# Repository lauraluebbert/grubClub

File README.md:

# grubClub
Please cite the information in this repository using the following DOI:  

I would like to present grubClub (“grub” for larva, and “club” for… well, you will see). I built off of the ethoscope (https://github.com/gilestrolab/ethoscope) by https://github.com/qgeissmann to enable automated long-term optogenetic stimulation of Drosophila larvae. Here is my Halloween-style release: https://twitter.com/NeuroLuebbert/status/1454220954666631170?s=20

GrubClub consists of a printed circuit board (PCB) and an accompanying arena. Both fit into the ethoscope published here: https://journals.plos.org/plosbiology/article?id=10.1371/journal.pbio.2003026.

The PCB holds 4 transistors, each connecting to 2 LEDs. Each row of LEDs can be controlled independently through Raspberry Pi GPIOs. In the picture below, each LED has a 270 ohm resistor. The power of the LEDs can be increased (or decreased) by modifying this resistance (within the circuit limits). 

The grubClub arena slides into the ethoscope and holds larvae in small round wells that can be filled with sugar-containing agar (or any larva medium). Each square fits a standard 22x22 mm coverslip as a lid. I 3D-printed my arena using translucent PLA to increase light intensity.

Since I am currently not recording larval behavior, I did not include an IR backlight for camera recordings. However, the PCB is designed such that an IR light strip can easily fit between the LED rows, enabling optogenetic stimulation and behavior recording at the same time. Finally, while red LEDs (~630 nm) might prevent a startle response, for my experimental design, I decided to stimulate at the spectral peak of my channelrhodopsin Chrimson (590 nm). The PCB supports LEDs of any color, and I included both options in the component list.

[grubClub PCB](https://user-images.githubusercontent.com/56094636/139601286-2ef72724-cccf-4f6b-9c9d-bd818d46505a.mp4)

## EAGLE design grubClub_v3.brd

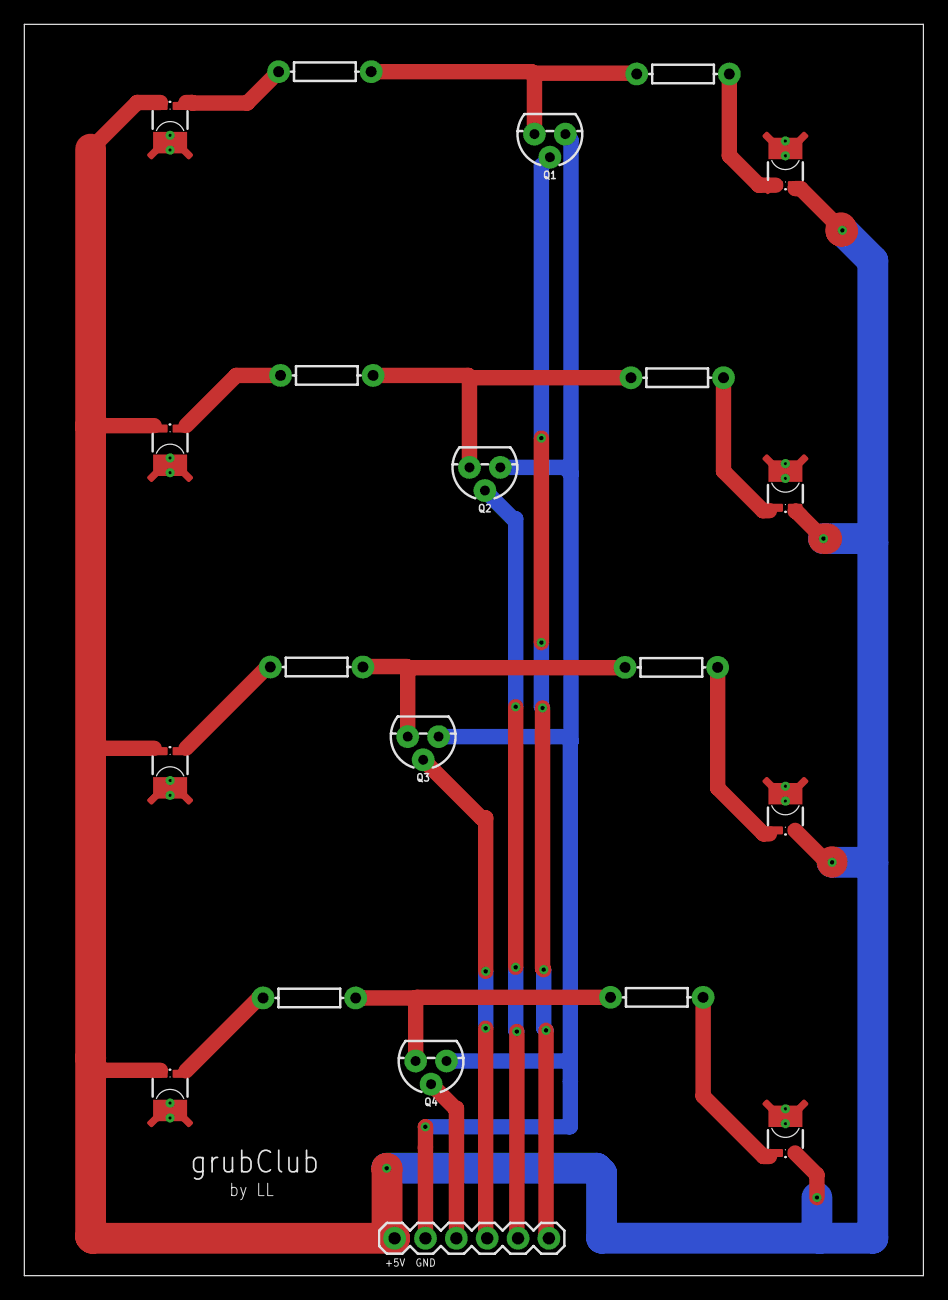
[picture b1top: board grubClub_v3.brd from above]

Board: 2 copper layers, 74.0 x 103.0 mm, 21 parts (0 on the bottom side), 20 nets.

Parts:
J6: 1X06
LED1, LED2, LED3, LED4, LED5, LED6, LED7, LED8: LUXEON_REBEL
Q1, Q2, Q3, Q4: 200mA/40V; TO-92
R1, R2, R3, R4, R5, R6, R7, R8: AXIAL-0.3

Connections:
unnamed: LED7.C, LED7.C@1, R1.P$1
unnamed: J6.4, Q4.2
unnamed: J6.3, Q3.2
unnamed: J6.2, Q2.2
unnamed: J6.1, Q1.2
unnamed: LED1.C, LED1.C@1, R4.P$1
unnamed: J6.6, LED1.A, LED1.A@1, LED2.A, LED2.A@1, LED3.A, LED3.A@1, LED4.A, LED4.A@1, LED6.A, LED6.A@1, LED7.A, LED7.A@1, LED8.A, LED8.A@1
unnamed: LED3.C, LED3.C@1, R3.P$1
unnamed: LED5.C, LED5.C@1, R2.P$1
unnamed: LED8.C, LED8.C@1, R6.P$2
unnamed: LED6.C, LED6.C@1, R7.P$2
unnamed: LED4.C, LED4.C@1, R8.P$2
unnamed: LED2.C, LED2.C@1, R5.P$2
unnamed: Q1.3, R4.P$2, R5.P$1
unnamed: Q2.3, R3.P$2, R8.P$1
unnamed: Q3.3, R2.P$2, R7.P$1
unnamed: Q4.3, R1.P$2, R6.P$1
unnamed: J6.5, Q1.1, Q2.1, Q3.1, Q4.1
S$1: LED5.A, LED5.A@1
TH: LED1.TH, LED1.TH@1, LED1.TH@2, LED1.TH@3, LED1.TH@4, LED2.TH, LED2.TH@1, LED2.TH@2, LED2.TH@3, LED2.TH@4, LED3.TH, LED3.TH@1, LED3.TH@2, LED3.TH@3, LED3.TH@4, LED4.TH, LED4.TH@1, LED4.TH@2, LED4.TH@3, LED4.TH@4, LED5.TH, LED5.TH@1, LED5.TH@2, LED5.TH@3, LED5.TH@4, LED6.TH, LED6.TH@1, LED6.TH@2, LED6.TH@3, LED6.TH@4, LED7.TH, LED7.TH@1, LED7.TH@2, LED7.TH@3, LED7.TH@4, LED8.TH, LED8.TH@1, LED8.TH@2, LED8.TH@3, LED8.TH@4

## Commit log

2021-10-29 Create LICENSE
2021-10-29 Added DOI
2021-10-29 Added DOI badge

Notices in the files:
parts and their libraries:
SparkFun-Connectors: Licensing: Creative Commons ShareAlike 4.0 International - https://creativecommons.org/licenses/by-sa/4.0
